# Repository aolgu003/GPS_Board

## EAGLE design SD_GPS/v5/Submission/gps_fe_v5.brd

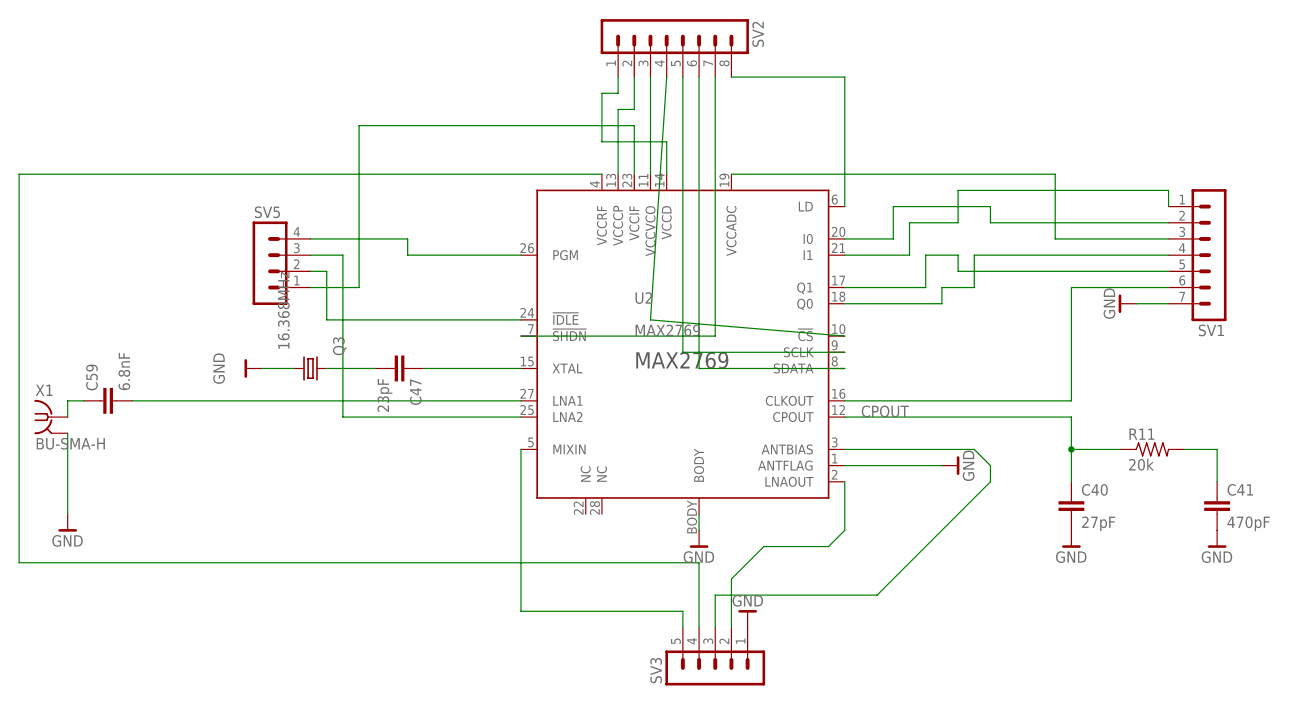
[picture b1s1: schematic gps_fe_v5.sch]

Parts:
C40: 27pF; C0402
C41: 470pF; C0402
C47: 23pF; C0402
C59: 6.8nF; C0402
Q3: 16.368MHz; CTS406
R11: 20k; R0402
SV1: MA07-1
SV2: MA08-1
SV3: MA05-1
SV5: MA04-1
U2: MAX2769; 90-0023
X1: BU-SMA-H

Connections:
BAR_GND: C40.2, C41.2, Q3.3 (2), SV1.7, SV3.1, U2.1 (ANTFLAG), U2.BODY, X1.2 (GND)
CPOUT: C40.1, R11.1, U2.12 (CPOUT)
GND: X1.3 (GND), X1.4 (GND), X1.5 (GND)
LNA3: C59.2, U2.27 (LNA1)
unnamed: SV1.5, U2.17 (Q1)
unnamed: C41.1, R11.2
unnamed: SV1.4, U2.18 (Q0)
unnamed: SV1.1, U2.21 (I1)
unnamed: SV1.2, U2.20 (I0)
unnamed: SV2.4, U2.10 (!CS)
unnamed: SV2.5, U2.9 (SCLK)
unnamed: SV2.6, U2.8 (SDATA)
unnamed: SV2.7, U2.7 (!SHDN)
unnamed: SV2.8, U2.6 (LD)
unnamed: SV1.6, U2.16 (CLKOUT)
unnamed: SV1.3, U2.19 (VCCADC)
unnamed: SV5.2, U2.24 (!IDLE)
unnamed: C47.2, Q3.1
unnamed: C59.1, X1.1
unnamed: SV5.4, U2.26 (PGM)
unnamed: SV3.2, U2.2 (LNAOUT)
unnamed: SV3.3, U2.3 (ANTBIAS)
unnamed: SV3.4, U2.4 (VCCRF)
unnamed: C47.1, U2.15 (XTAL)
unnamed: SV3.5, U2.5 (MIXIN)
unnamed: SV5.1, U2.23 (VCCIF)
unnamed: SV2.3, U2.11 (VCCVCO)
unnamed: SV2.2, U2.13 (VCCCP)
unnamed: SV5.3, U2.25 (LNA2)
unnamed: SV2.1, U2.14 (VCCD)

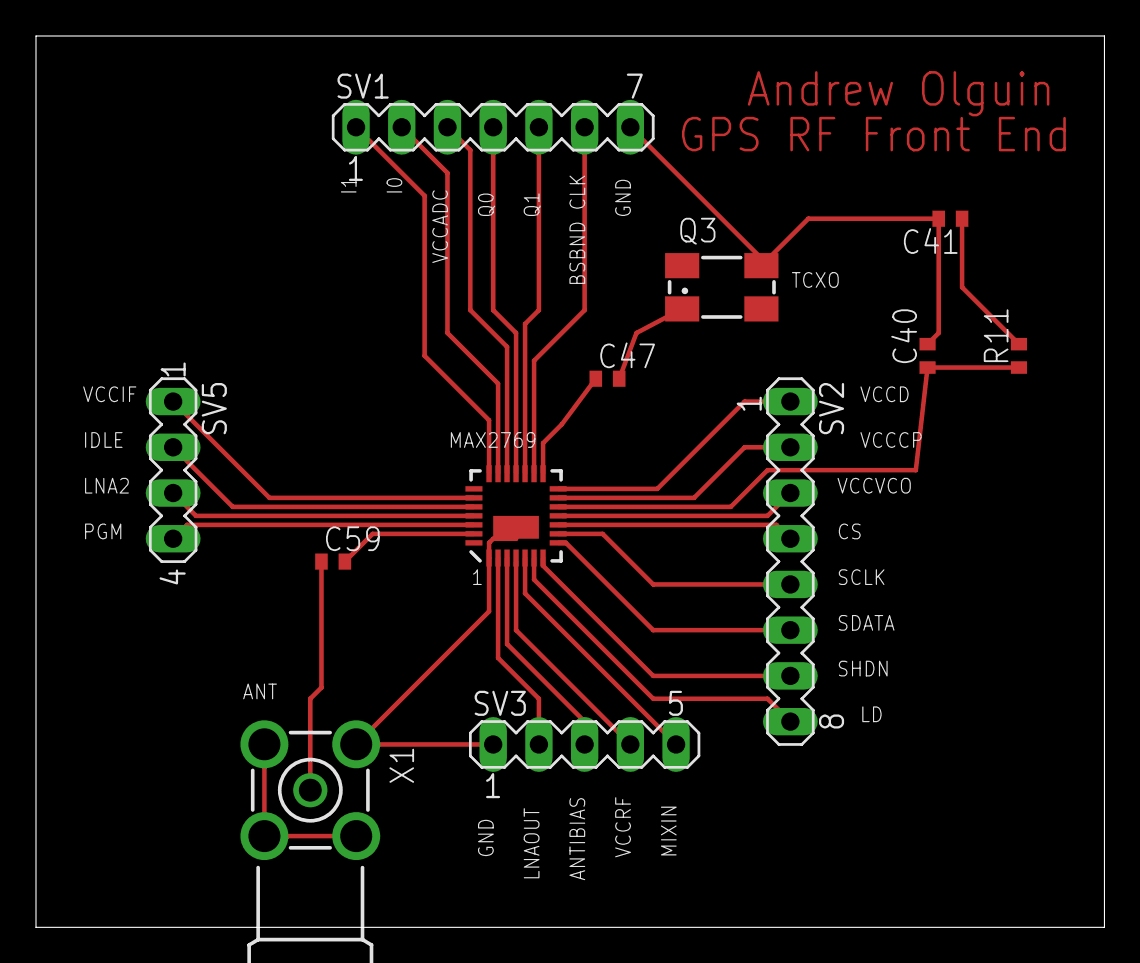
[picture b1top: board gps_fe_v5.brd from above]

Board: 2 copper layers, 59.4 x 49.5 mm, 12 parts (0 on the bottom side), 30 nets.

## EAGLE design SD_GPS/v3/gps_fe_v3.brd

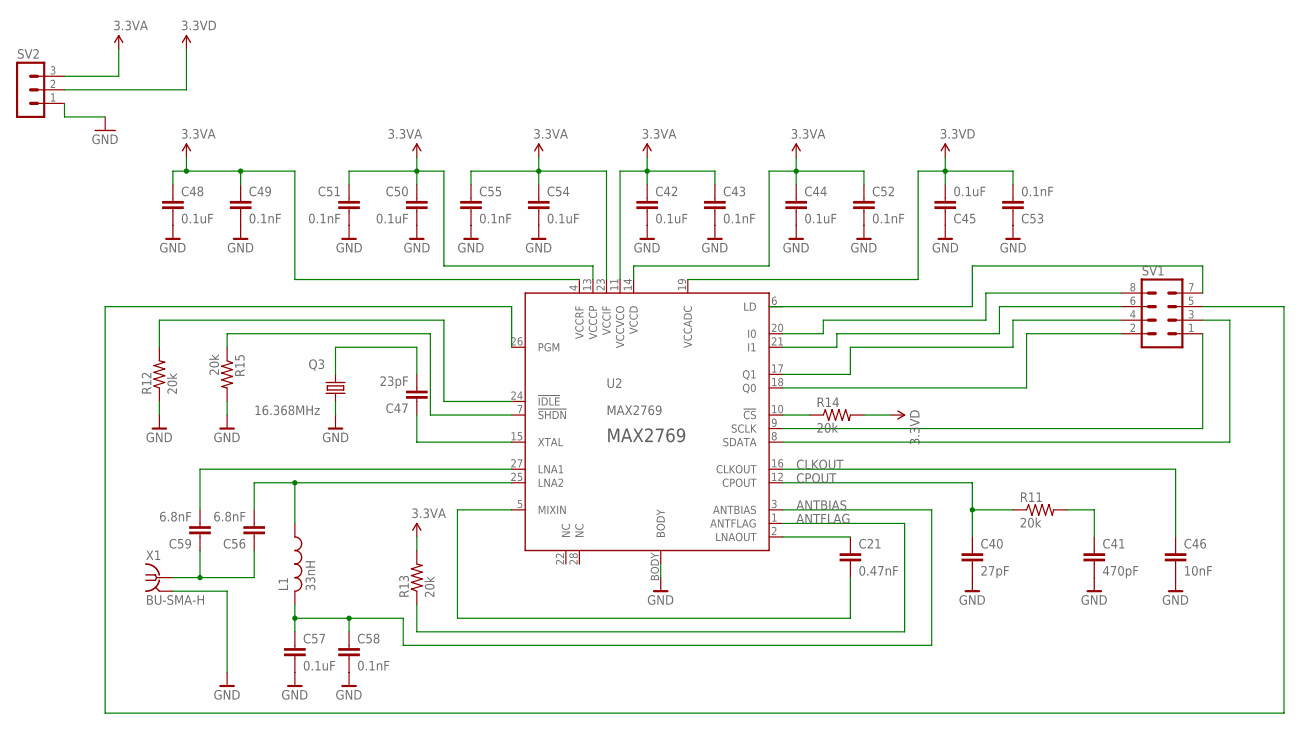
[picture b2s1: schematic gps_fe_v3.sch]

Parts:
C21: 0.47nF; C0402
C40: 27pF; C0402
C41: 470pF; C0402
C42, C44, C45, C48, C50, C54, C57: 0.1uF; C0402
C43, C49, C51, C52, C53, C55, C58: 0.1nF; C0402
C46: 10nF; C0402
C47: 23pF; C0402
C56, C59: 6.8nF; C0402
L1: 33nH; 0402-A
Q3: 16.368MHz; CTS406
R11, R12, R13, R14, R15: 20k; R0402
SV1: MA04-2
SV2: MA03-1
U2: MAX2769; 90-0023
X1: BU-SMA-H

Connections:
3.3VA: C42.1, C43.1, C44.1, C48.1, C49.1, C50.1, C51.1, C52.1, C54.1, C55.1, R13.2, SV2.3, U2.4 (VCCRF), U2.11 (VCCVCO), U2.13 (VCCCP), U2.14 (VCCD), U2.23 (VCCIF)
3.3VD: C45.2, C53.2, R14.2, SV2.2, U2.19 (VCCADC)
ANTBIAS: C57.1, C58.1, L1.2, U2.3 (ANTBIAS)
ANTFLAG: R13.1, U2.1 (ANTFLAG)
BAR_GND: C40.2, C41.2, C42.2, C43.2, C44.2, C45.1, C46.2, C48.2, C49.2, C50.2, C51.2, C52.2, C53.1, C54.2, C55.2, C57.2, C58.2, Q3.3 (2), R12.1, R15.2, U2.BODY, X1.2 (GND)
CLKOUT: C46.1, U2.16 (CLKOUT)
CPOUT: C40.1, R11.1, U2.12 (CPOUT)
GND: SV2.1, X1.3 (GND), X1.4 (GND), X1.5 (GND)
LNA3: C59.2, U2.27 (LNA1)
LNA4: C56.2, L1.1, U2.25 (LNA2)
LNAOUT1: C21.1, U2.2 (LNAOUT)
unnamed: SV1.5, U2.26 (PGM)
unnamed: C41.1, R11.2
unnamed: SV1.8, U2.20 (I0)
unnamed: SV1.6, U2.21 (I1)
unnamed: SV1.4, U2.17 (Q1)
unnamed: R14.1, U2.10 (!CS)
unnamed: SV1.2, U2.18 (Q0)
unnamed: SV1.1, U2.9 (SCLK)
unnamed: SV1.3, U2.8 (SDATA)
unnamed: C47.2, Q3.1
unnamed: C56.1, C59.1, X1.1
unnamed: R15.1, U2.7 (!SHDN)
unnamed: R12.2, U2.24 (!IDLE)
unnamed: C21.2, U2.5 (MIXIN)
unnamed: C47.1, U2.15 (XTAL)

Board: 2 copper layers, 32 parts (0 on the bottom side), 26 nets, no tracks yet.

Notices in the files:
parts and their libraries:
SparkFun-Aesthetics: Licensing: CC v3.0 Share-Alike You are welcome to use this library for commercial purposes.
